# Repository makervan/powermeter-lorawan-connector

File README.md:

# DC Power Meter LoRaWAN Connector Node
LoRaWAN node to send data from the GC90/GC91 DC power meters via TTN. Based on an Arduino Pro Mini and the RFM95 LoRa module.

## Hardware
* Arduino Pro Mini 3.3V 8Mhz
* RFM95/96 LoRaWAN module
* [uFL socket](https://www.digikey.de/product-detail/en/linx-technologies-inc/CONUFL001-SMD-T/CONUFL001-SMD-TCT-ND/7427733) or edge mount SMA socket
* 2 BSS138 MOSFETs (Q1/Q2) and 2x 10k resistors (R3/R4, 0805) for the level shifter
* USB A socket
* 2 resistors (R1/R2, 0805) to form a voltage divider for measuring the input voltage (optional, values depending on voltage range)
* Groove connector (optional)

## Payload decoder
If you use the TTN network, you can use the following payload decoder:

```
function Decoder(bytes, port) {
  // Decode an uplink message from a buffer
  // (array) of bytes to an object of fields.
  var decoded = {};
  decoded.voltage = (bytes[2] << 8 | bytes[1]) / 100;
  decoded.current = (bytes[4] << 8 | bytes[3]) / 1000;
  decoded.usage = (bytes[8] << 24 | bytes[7] << 16 | bytes[6] << 8 | bytes[5]) / 1000;
  decoded.cum_usage = (bytes[12] << 24 | bytes[11] << 16 | bytes[10] << 8 | bytes[9]) / 1000;

  return decoded;
}
```

## License
* Hardware is based off a design by [Doug Larue](https://github.com/dlarue) with additions by me, Severin Schols. It's licensed under Creative Commons Attribution-ShareAlike 4.0 International License (CC BY-SA 4.0)
* Software (firmware and the payload decoder) are licensed under MIT License

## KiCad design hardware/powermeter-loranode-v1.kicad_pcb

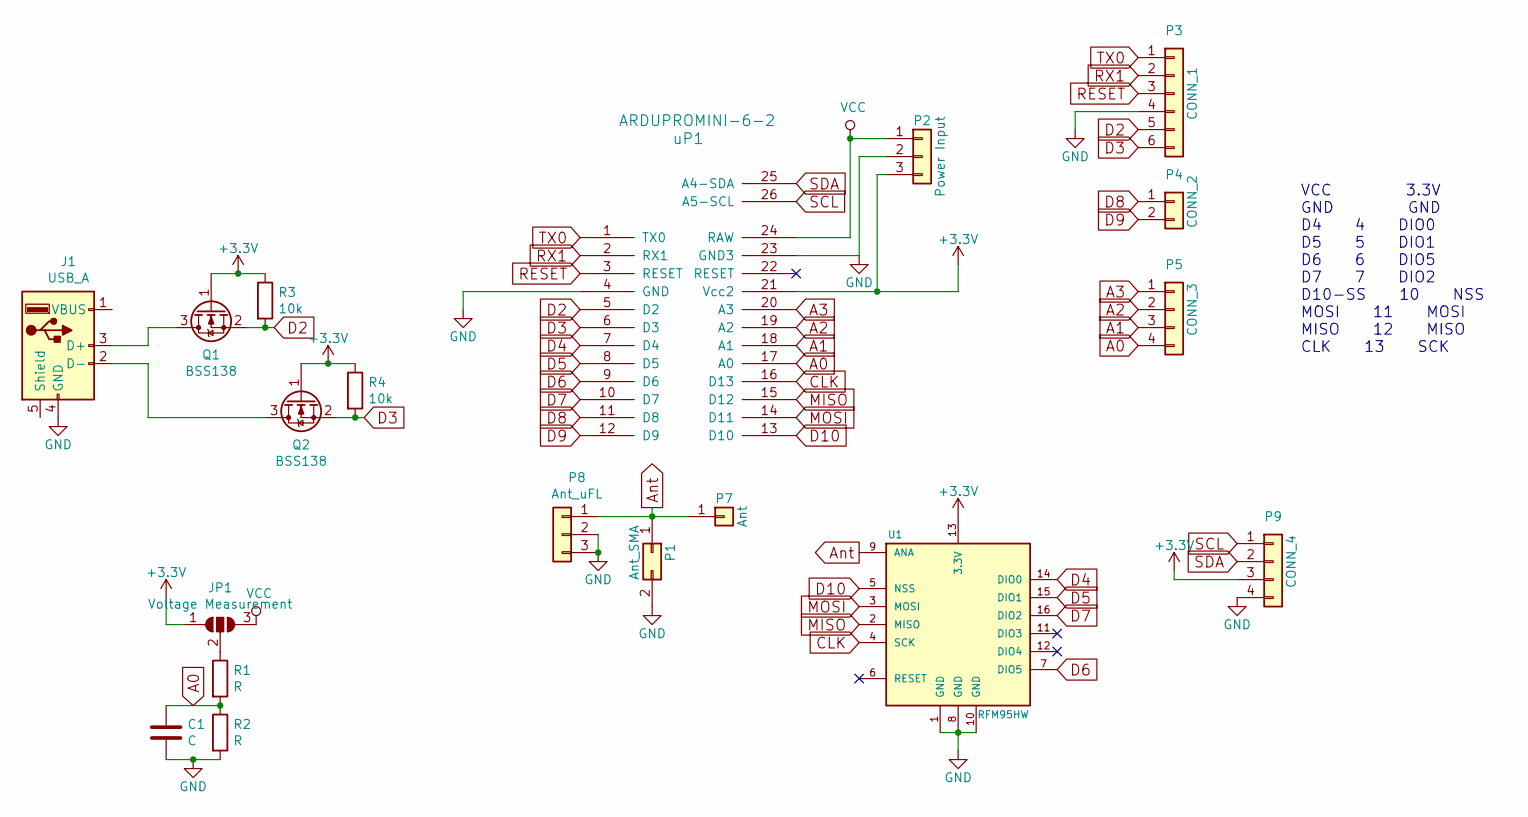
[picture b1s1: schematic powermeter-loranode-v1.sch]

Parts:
C1: C; C_0805_2012Metric_Pad1.15x1.40mm_HandSolder
J1: USB_A; USB_A_Stewart_SS-52100-001_Horizontal
JP1: Voltage Measurement; SolderJumper-3_P1.3mm_Open_RoundedPad1.0x1.5mm_NumberLabels
P1: Ant_SMA; SMA_EDGE
P2: Power Input; PINHEAD1-3
P3: CONN_1; Pin_Header_Straight_1x06
P4: CONN_2; Pin_Header_Straight_1x02
P5: CONN_3; Pin_Header_Straight_1x04
P7: Ant; PINTST
P8: Ant_uFL; U.FL-COAX
P9: CONN_4; NS-Tech_Grove_1x04_P2mm_Vertical
Q1, Q2: BSS138; SOT-23
R1, R2: R; R_0805_2012Metric_Pad1.15x1.40mm_HandSolder
R3, R4: 10k; R_0805_2012Metric_Pad1.15x1.40mm_HandSolder
U1: RFM95HW; RFM69HW_SMD_Handsoldering-Narrow
uP1: ARDUPROMINI-6-2; pro_mini-26

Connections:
+3V3: JP1.1 (A), P2.3, P9.3, Q1.1 (G), Q2.1 (G), R3.1, R4.1, U1.13 (3.3V), uP1.21 (Vcc2)
A0: C1.1, P5.4, R1.2, R2.1, uP1.17 (A0)
A1: P5.3, uP1.18 (A1)
A2: P5.2, uP1.19 (A2)
A3: P5.1, uP1.20 (A3)
Ant: P1.1, P7.1, P8.1, U1.9 (ANA)
CLK: U1.4 (SCK), uP1.16 (D13)
D2: P3.5, Q1.2 (S), R3.2, uP1.5 (D2)
D3: P3.6, Q2.2 (S), R4.2, uP1.6 (D3)
D4: U1.14 (DIO0), uP1.7 (D4)
D5: U1.15 (DIO1), uP1.8 (D5)
D6: U1.7 (DIO5), uP1.9 (D6)
D7: U1.16 (DIO2), uP1.10 (D7)
D8: P4.1, uP1.11 (D8)
D9: P4.2, uP1.12 (D9)
D10: U1.5 (NSS), uP1.13 (D10)
GND: C1.2, J1.4 (GND), P1.2, P2.2, P3.4, P8.2, P8.3, P9.4, R2.2, U1.1 (GND), U1.8 (GND), U1.10 (GND), uP1.4 (GND), uP1.23 (GND3)
MISO: U1.2 (MISO), uP1.15 (D12)
MOSI: U1.3 (MOSI), uP1.14 (D11)
unnamed: J1.2 (D-), Q2.3 (D)
unnamed: J1.3 (D+), Q1.3 (D)
unnamed: JP1.2 (C), R1.1
RESET: P3.3, uP1.3 (RESET)
RX1: P3.2, uP1.2 (RX1)
SCL: P9.1, uP1.26 (A5-SCL)
SDA: P9.2, uP1.25 (A4-SDA)
TX0: P3.1, uP1.1 (TX0)
VCC: JP1.3 (B), P2.1, uP1.24 (RAW)

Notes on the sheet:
VCC 3.3V GND GND D4 4 DIO0 D5 5 DIO1 D6 6 DIO5 D7 7 DIO2 D10-SS 10 NSS MOSI 11 MOSI MISO 12 MISO CLK 13 SCK

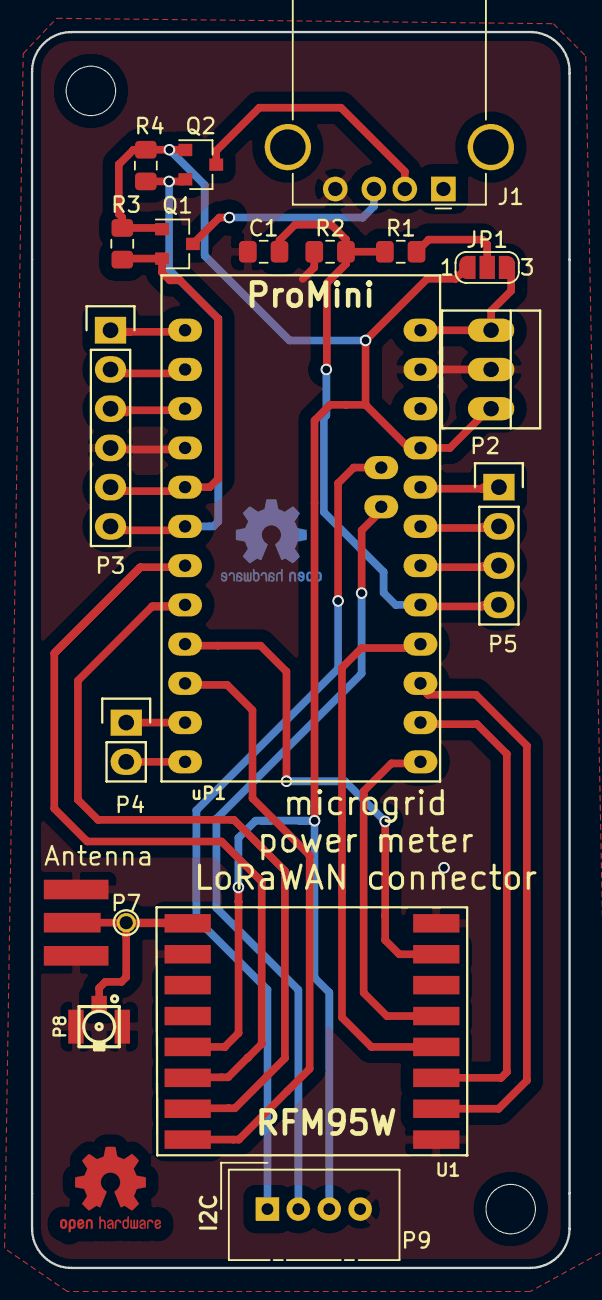
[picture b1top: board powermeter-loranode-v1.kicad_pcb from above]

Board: 2 copper layers, 34.8 x 80.0 mm, 19 parts (0 on the bottom side), 28 nets.

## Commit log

2019-10-24 initial commit, hardware only
2020-12-30 firmware + payload decoder
